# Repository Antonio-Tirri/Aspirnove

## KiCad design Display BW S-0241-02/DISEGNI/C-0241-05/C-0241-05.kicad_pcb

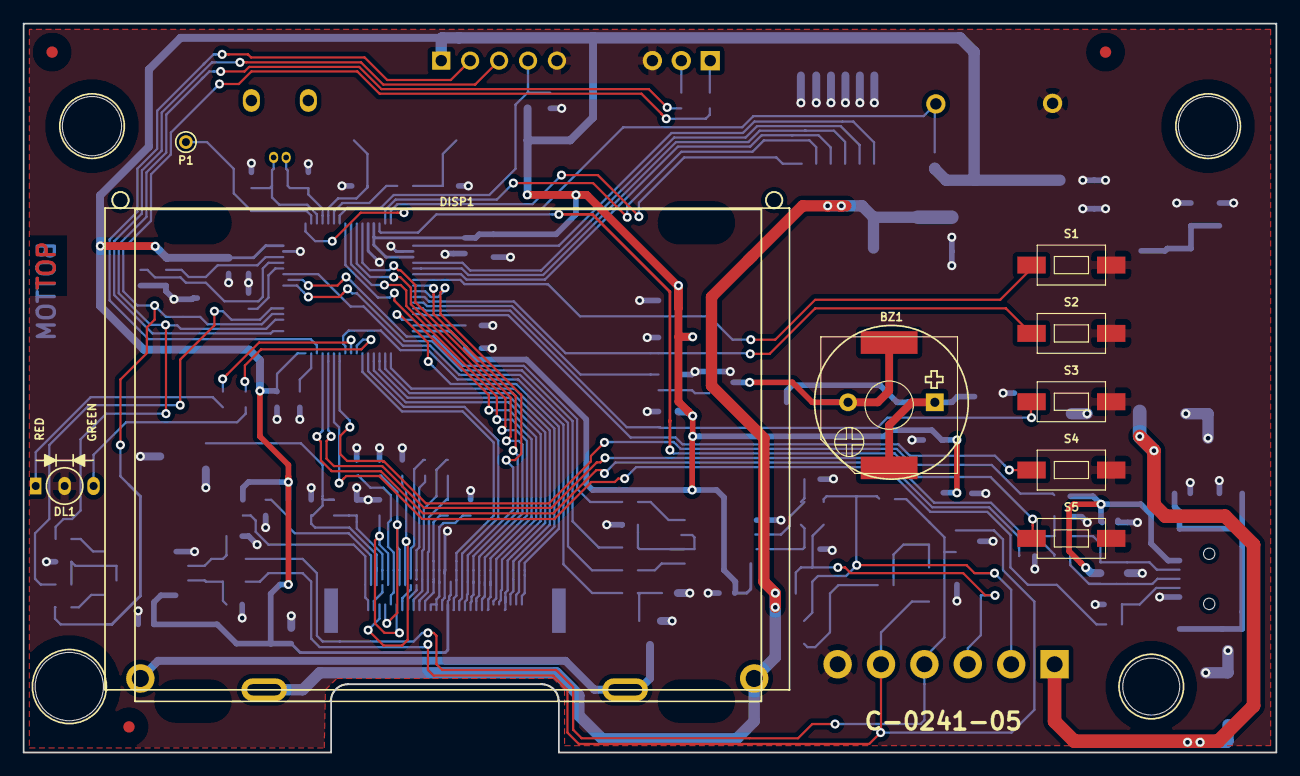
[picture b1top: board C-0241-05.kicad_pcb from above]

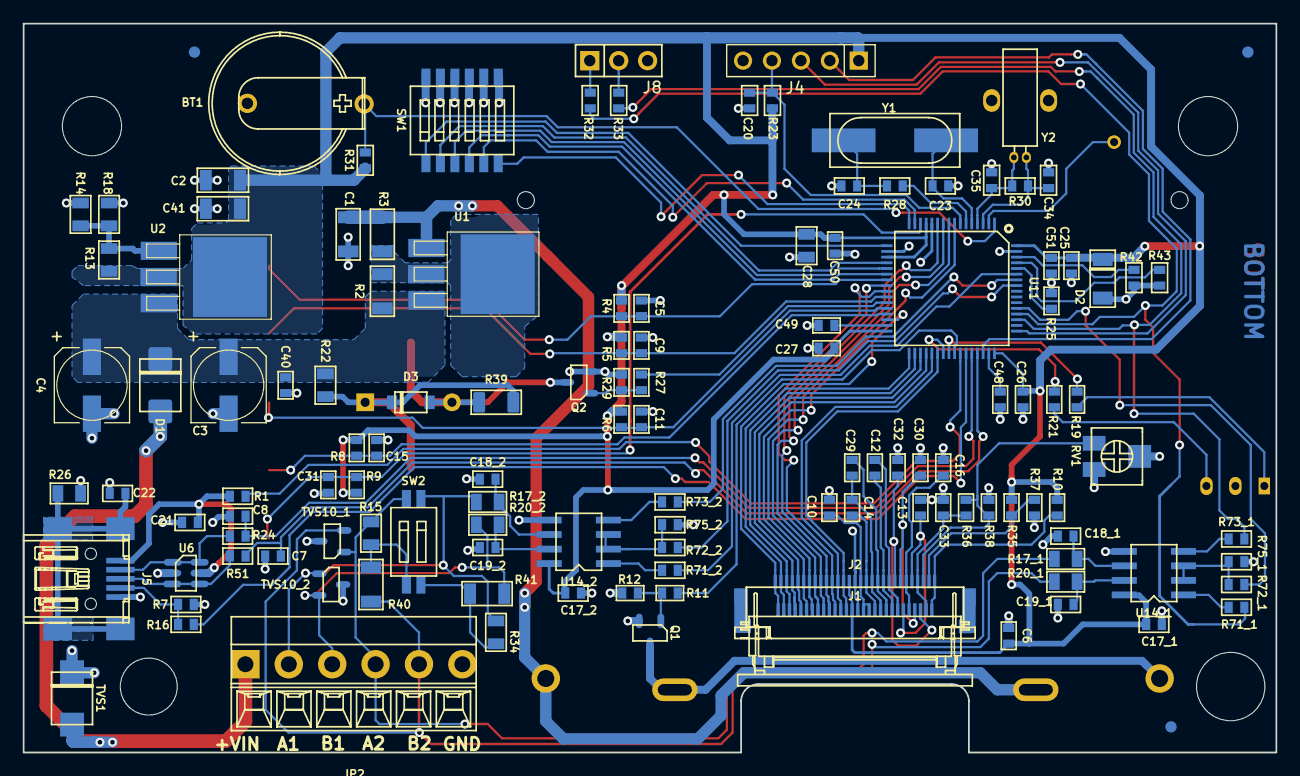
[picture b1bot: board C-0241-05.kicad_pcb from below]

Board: 2 copper layers, 110.0 x 64.0 mm, 135 parts (124 on the bottom side), 101 nets.

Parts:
BT1: CR-1220/HFN; CR1220_HFN
BZ1: LPT1230S-HL-03-4.0-1; KPEG242
BZ1A: LPT1230S-HL-03-4.0-1
C1, C2, C41: 10uF; C1206
C3, C4: 47uF; ELE-D-660
C5, C9, C11, C13, C15, C16, C20, C21, C22, C25, C26, C27, C30, C31, C32, C33, C40, C50, C51: 100nF; C0603
C6, C10, C12, C14, C17_1, C17_2, C29: 1uF; C0603
C7, C8, C23, C24, C34, C35: 12pF; C0603
C18_1, C18_2, C19_1, C19_2: 1nF; C0603
C28: 4.7uF; C0805
C48, C49: 2.2uF; C0603
D1: S2M; D_SMB_DO-214AA_AK
D2: 3.9VZ; D_MiniMELF_SOD80_AK
D3: 1N4148; D_SOD-123_AK
DISP1: G64128W20NBW00; CCT_G64128W20NBW00
DISP2: RX12864A1-BIW; RAYSTAR_RX12864A1-YHY
DL1: BILED; KINGBRIGHT_L-93WSURKCGKC_A1A2K
J1: 52437-2833; Molex_52437-2833
J2: 52435-2933; Molex_52435-2933_Special_Display_RX12864A1-YHY
J4: STRIP2.54-1X5-H11.6-M; SIX5
J5: 65100516121; WURTH_65100516121
J8: STRIP2.54-1X3-H11.6-M; SIX3
JP2: 691508110306; WURTH_691221320006
P1: PAD; PAD_1.2mm_H0.7mm
Q1, Q2: BC817; SOT-23
R1, R7, R16, R25, R31, R42, R43: 0; R0603
R2: 0; R1206
R3: 33; R1206
R4, R5, R6, R8, R9, R10, R12, R23, R29, R35, R37, R75_1, R75_2: 10K; R0603
R11, R27: 22K; R0603
R13: 470; R0805
R14, R18: 1.5K; R0805
R15, R34: 0; R0805
R17_1, R17_2, R20_1, R20_2: 4.7; R0805
R19, R21: 100; R0603
R22: 10; R0805
R24, R51: 10; R0603
R26: 1M; R0805
R28: 220; R0603
R30: 1M; R0603
R32, R33, R71_1, R71_2, R72_1, R72_2, R73_1, R73_2: 1K; R0603
R36: 1.8M; R0603
R38: 330K; R0603
R39: 2.2K; R1206
R40, R41: 120; R1206
RV1: 1M; BOURNS_3314J-1
S1, S2, S3, S4, S5: TVBM11
SW1: GDH06S04; TE_GDH06S04
SW2: GDH02S04; TE_GDH02S04
TVS1: SM6T18CA; D_SMB_DO-214AA
TVS10_1, TVS10_2: CDSOT23-SM712; SOT-23
U1, U2: LM1117IDTX-ADJ/NOPB; TO-252-3Lead_4TAB
U6: USBLC6-2SC6; SOT-23-6_SC74
U11: STM32F205RCT6; QFP-64_10x10mm_Pitch0.5mm
U14_1, U14_2: SN65HVD75D; SOIC-8_3.9x4.9mm_Pitch1.27mm
Y1: 12MHz; Crystal_SMD_HC49
Y2: 32.768kHz; AB38T_Horizontal_Reverse

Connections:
512Hz_OUT: P1.1, U11.2
BL-: DISP1.K, DISP2.K, Q1.3
BUZZER: R27.1, U11.27
C1+: C29.1, J1.20, J2.11
C1-: C14.1, C29.2, J1.19, J2.12
C2+: C12.1, J1.21, J2.10
C2-: C12.2, J1.22, J2.9
C3+: C14.2, J1.18, J2.13
DIP_1: SW1.1, U11.17
DIP_2: SW1.2, U11.20
DIP_3: SW1.3, U11.21
DIP_4: SW1.4, U11.22
DIP_5: SW1.5, U11.15
DIP_6: SW1.6, U11.16
GND: BT1.-, C1.2, C2.2, C3.2, C4.2, C5.1, C6.1, C7.2, C8.2, C9.1, C10.1, C11.1, C13.2, C15.1, C16.2, C17_1.2, C17_2.2, C18_1.2, C18_2.2, C19_1.2, C19_2.2, C20.2, C21.2, C22.2, C23.2, C24.2, C25.2, C26.2, C27.2, C28.2, C30.2, C31.1, C32.2, C33.2, C34.2, C35.2, C40.2, C41.2, C48.2, C49.2, C50.2, C51.2, D2.A, DL1.K, J1.15, J2.15, J4.5, J5.5, J8.3, JP2.6, Q1.2, Q2.2, R7.2, R12.2, R14.2, R18.2, R25.1, R26.2, R29.2, R37.1, R38.1, R42.2, R43.2, R75_1.2, R75_2.2, RV1.1, RV1.2, S1.1, S2.1, S3.1, S4.1, S5.1, SW1.7, SW1.8, SW1.9, SW1.10, SW1.11, SW1.12, TVS1.1, TVS10_1.3, TVS10_2.3, U6.2, U11.12, U11.18, U11.63, U14_1.5, U14_2.5
HW_SEL0: R43.1, U11.61
HW_SEL1: R42.1, U11.62
JTAG_RESET: C20.1, J4.4, R23.2, U11.7
JTAG_SWCLK: J4.3, U11.49
JTAG_SWDIO: J4.2, U11.46
LCD_CLR: J1.2, J2.28, U11.33
LCD_CS: J1.1, J2.29, U11.30
LCD_D0: J1.6, J2.24, U11.8
LCD_D1: J1.7, J2.23, U11.9
LCD_D2: J1.8, J2.22, U11.10
LCD_D3: J1.9, J2.21, U11.11
LCD_D4: J1.10, J2.20, U11.24
LCD_D5: J1.11, J2.19, U11.25
LCD_D6: J1.12, J2.18, U11.37
LCD_D7: J1.13, J2.17, U11.38
LCD_EN: J1.5, J2.25, U11.36
LCD_PWM: R11.1, U11.41
LCD_RS: J1.3, J2.27, U11.34
LCD_RW: J1.4, J2.26, U11.35
LED_R: R19.2, U11.40
LED_V: R21.2, U11.39
NetBT1_+: BT1.+, R31.1, U11.1
NetBZ1_1: BZ1.1, BZ1A.1, D3.K, R22.1, R39.1
NetBZ1_2: BZ1.2, BZ1A.2, D3.A, Q2.3, R39.2
NetC18_1_1: C18_1.1, R17_1.2, U14_1.6
NetC18_2_1: C18_2.1, R17_2.2, U14_2.6
NetC19_1_1: C19_1.1, R20_1.2, U14_1.7
NetC19_2_1: C19_2.1, R20_2.2, U14_2.7
NetC22_1: C22.1, J5.S, R26.1
NetC23_1: C23.1, U11.5, Y1.1
NetC24_1: C24.1, R28.2, Y1.2
NetC34_1: C34.1, R30.2, U11.3, Y2.1
NetC35_1: C35.1, R30.1, U11.4, Y2.2
NetC48_1: C48.1, U11.47
NetC49_1: C49.1, U11.31
NetDL1_A1: DL1.A1, R19.1
NetDL1_A2: DL1.A2, R21.1
NetJ2_2: J2.2, R35.1, R37.2
NetJ2_3: J2.3, R36.1, R38.2, RV1.3
NetJ5_4: J5.4, R7.1, R16.1
NetJ8_1: J8.1, R32.1
NetJ8_2: J8.2, R33.1
NetQ1_1: Q1.1, R11.2, R12.1
NetQ2_1: Q2.1, R27.2, R29.1
NetR1_2: R1.2, U11.42
NetR2_1: R2.1, R3.2, U1.2, U1.4
NetR13_2: R13.2, R14.1, R18.1, U2.1
NetR15_2: R15.2, R40.2, SW2.3
NetR25_2: R25.2, U11.60
NetR28_1: R28.1, U11.6
NetR34_2: R34.2, R41.2, SW2.4
NetR71_1_1: R71_1.1, U14_1.1
NetR71_2_1: R71_2.1, U14_2.1
NetR72_1_2: R72_1.2, R75_1.1, U14_1.2, U14_1.3
NetR72_2_2: R72_2.2, R75_2.1, U14_2.2, U14_2.3
NetR73_1_2: R73_1.2, U14_1.4
NetR73_2_2: R73_2.2, U14_2.4
PS: J1.28, J2.1, R10.1
RS485_A_1: JP2.4, R15.1, R17_1.1, SW2.2, TVS10_1.1
RS485_A_2: JP2.2, R17_2.1, R34.1, SW2.1, TVS10_2.1
RS485_B_1: JP2.5, R20_1.1, R40.1, TVS10_1.2
RS485_B_2: JP2.3, R20_2.1, R41.1, TVS10_2.2
RS485_DIR_1: R72_1.1, R72_2.1, U11.53, U11.57
RS485_RX_1: R32.2, R71_1.2, R71_2.2, U11.52, U11.59
RS485_TX_1: R33.2, R73_1.1, R73_2.1, U11.51, U11.58
SW1: C5.2, R4.2, S1.2, U11.23
SW2: C9.2, R5.2, S2.2, U11.26
SW3: C11.2, R6.2, S3.2, U11.28
SW4: C15.2, R8.2, S4.2, U11.29
SW5: C31.2, R9.2, S5.2, U11.14
USB_DN: C8.1, R24.1, U11.44
USB_DP: C7.1, R51.1, U11.45
USB_ID: R16.2, U11.43
USB_N: J5.2, R24.2, U6.1, U6.6
USB_P: J5.3, R51.2, U6.3, U6.4
V0: C33.1, J1.27, J2.4, R36.2
V1: C13.1, J1.23, J2.5
V2: C16.1, J1.24, J2.6
V3: C30.1, J1.25, J2.7
V4: C32.1, J1.26, J2.8
VCC_3V3: C2.1, C6.2, C17_1.1, C17_2.1, C25.1, C26.1, C27.1, C28.1, C41.1, C50.1, C51.1, D2.K, J1.14, J2.16, J4.1, R4.1, R5.1, R6.1, R8.1, R9.1, R10.2, R13.1, R23.1, R31.2, R35.2, U2.2, U2.4, U11.13, U11.19, U11.32, U11.48, U11.64, U14_1.8, U14_2.8
VCC_12V: C3.1, C4.1, C40.1, D1.K, R2.2, R22.2, U1.3, U2.3
VCC_ALIM: D1.A, JP2.1, TVS1.2
VCC_BACKLIGHT: C1.1, DISP1.A, DISP2.A, R3.1, U1.1
VCC_VUSB: C21.1, J5.1, R1.1, U6.5
VOUT: C10.2, J1.16, J1.17, J2.14

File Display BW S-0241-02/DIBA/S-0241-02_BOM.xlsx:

Progetto: |  |  | Scheda Display
Codice scheda: |  |  | S-0241-02
Variante: |  |  | 002
Revisione: |  |  | 02
Data report: |  |  | 13/11/2020 | Agg.: | 10/11/2021 | 15/12/2021
# | Riferimento | Valore | Descrizione | Costruttore | P/N Costruttore | Contenitore | Quantità | Note
# | Designator | Value | Description | Manufacturer | Manufacturer Part Number | Package | Quantity | AssemblyNotes
1 |  |  |  |  |  |  | 1 | ELC-0241-05
2 | BZ1 | LPT1230S-HL-03-4.0-1 | Piezo Buzzer | Cre-sound | LPT1230S-HL-03-4.0-1 | SMD | 1 | REBZ90003
3 | C1, C2, C41 | 10uF 25V | MLCC Capacitor, 10uF 25V, ±10%, X7R, Case 1206 | Avx | 12063C106KAT2A | 1206 | 3 | RECD93014
4 | C3, C4 | 47uF 25V | SMD Aluminum Electrolytic Capacitor, 47uF 25V, 6.3mm x 5.8mm | Panasonic | EEEFK1E470P | SMD 6.3mm x 5.8mm | 2 | RECD81000
5 | C5, C9, C11, C13, C15, C16, C30, C31, C32, C33 C20, C21, C22, C25, C26, C27, C4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 | 100nF 50V | Multilayer Ceramic Capacitor | Panasonic / TDK / Kemet | ECJ1VB1H104 | 0603 | 19 | RECD95018
6 | C6, C10, C12, C14, C29 C17_1, C17_2 | 1uF 50V | Multilayer Ceramic Chip Capacitor, 1uF 50V, 0603, X7R, 10% | Panasonic / TDK / Kemet | CGA3E2X7R1H102K080AD | 0603 | 7 | RECD95033
7 | C7, C8, C23, C24 | 12pF 50V | MLCC Capacitor, 12pF 50V, ±10%, C0G, Case 0603 | AVX Corp. | 06035A120KAT2A | 0603 | 4 | RECD95026
8 | C18_1, C18_2, C19_1, C19_2 | 1nF 50V | MLCC Capacitor, 1nF 50V, ±10%, C0G, Case 0603 | Avx | 06035C102KAT2A | 0603 | 4 | RECD95011
9 | C28 | 4.7uF 16V | MLCC Capacitor, 4.7uF 16V, ±10%, X7R, Case 0805 | Avx | 0805YC475KAT2A | 0805 | 1 | RECD92028
10 | C48, C49 | 2.2uF 25V | MLCC Capacitor, 2.2uF 25V, ±10%, X5R, Case 0603 | Samsung | CL10A225KA8NNNC | 0603 | 2 | RECD95023
11 | D1 | S2M | Rectifier Diode, 1KV, 1.5A, SMB | DC Components | S2M | SMB | 1 | REDD91002
12 | D3 | 1N4148 | Small Signal Diode, 100V, 150mA, SOD-123 | Diodes Inc. | 1N4148W-7-F | SOD123 | 1 | REDD91035
13 | DISP1 | G64128W20NBW00 | LCD Graphic Display, 128x64, Blue | CCT | G64128W20NBW00 | MECH | 1 | ELC-0241-05
14 | DL1 | BILED 3mm | BICOLOR LED 3mm common cathode | Kingbright | L-93WSURKCGKC | PTH | 1 | A-1132-00
15 | J1 |  | FFC/FPC Connector 29-way | Molex |  | SMD | 1 | RECN90024
16 | J4 | STRIP2.54-1X5-H11.6-M | 5-Way Pin Strip, Single Row, 2.54mm pitch, Male | Adimpex | LE022005-R | PTH | 1 | A-0559-00
17 | J5 | 65100516121 | Mini-USB connector, Type B , Vertical, PTH | Wurth | 65100516121 | SMD | 1 | RECN90017
18 | JP2 | 691221320006 | Morsettiera 6vie , passo 3.5mm, SMD | Wurth | 691221320006 | PTH | 1 | A-1308-00
19 | Q1, Q2 | BC817 | NPN Silicon Transistor, Small signals | NXP Semiconductors | BC817 | SOT-23 | 2 | RETR93010
20 | R1, R7, R16, R25, R31, R42, R43 | 0 | SMD Resistor, 0R, Case 0603 | Vishay | CRCW06030000Z0TABC | 0603 | 7 | RERS95000
21 | R18 | 1.5K 1% | SMD Resistor, 1.5K, Tolerance 1%, Case 0805 |  | CRCW08051K50FKTABC | 0805 | 1 | RERS93108
22 | R3 | 33 1% | SMD Resistor, 33 Ohm, Tolerance 1%, Case 1206 | Vishay | CRCW120633R0FKTA | 1206 | 1 | RERS91095
23 | R4, R5, R6, R8, R9, R75_1, R75_2, R10, R12,R23, R29 | 10K 1% | SMD Resistor, 10K, Tolerance 1%, Case 0603 | Vishay | CRCW060310K0FKTABC | 0603 | 12 | RERS95570
24 | R11, R27 | 22K 1% | SMD Resistor, 22K, Tolerance 1%, Case 0603 | Vishay | CRCW060322K0FKTABC | 0603 | 2 | RERS95576
25 | R13 | 470 1% | SMD Resistor, 470 Ohm, Tolerance 1%, Case 0805 | Vishay | CRCW0805470RFKTABC | 0805 | 1 | RERS93116
26 | R14 | 1.5K 1% | SMD Resistor, 1.5K, Tolerance 1%, Case 0805 | Vishay | CRCW08051K50FKTABC | 0805 | 1 | RERS93108
27 | R17_1, R17_2, R20_1, R20_2 | 4.7 1% | SMD Resistor, 4.7 Ohm, Tolerance 1%, Case 0805 | Vishay | CRCW080544R70FKTABC | 0805 | 4 | RERS93110
28 | R19, R21 | 100 1% | SMD Resistor, 100 Ohm, Tolerance 1%, Case 0603 | Vishay | CRCW0603100RFKTABC | 0603 | 2 | RERS95510
29 | R22 | 10 1% | SMD Resistor, 10 Ohm, Tolerance 1%, Case 0805 | Vishay | CRCW080510R0FKTABC | 0805 | 1 | RERS93000
30 | R24, R51 | 10 1% | SMD Resistor, 10Ohm, Tolerance 1%, Case 0603 | Vishay | CRCW060310R0FKTABC | 0603 | 2 | RERS95500
31 | R26 | 1M 1% | SMD Resistor, 1M, Tolerance 1%, Case 0805 | Vishay | CRCW08051M00FKTA | 0805 | 1 | RERS93050
32 | R36 | 1.8M 1% | RES. SMD 1,8M 0603 1% |  |  | 0603 | 1 | RERS95609
33 | R38 | 330K 1% | RES. SMD 330K 0603 1% |  |  | 0603 | 1 | RERS95610
34 | R28 | 220 1% | SMD Resistor, 220 Ohm, Tolerance 1%, Case 0603 | Vishay | CRCW0603220RFKTABC | 0603 | 1 | RERS95009
35 | R32, R33, R71_1, R71_2 ,R72_1, R72_2, R73_1, R73_2 | 1K 1% | SMD Resistor, 1K, Tolerance 1%, Case 0603 | Vishay | CRCW06031K00FKTABC | 0603 | 8 | RERS95550
36 | R39 | 2.2K 1% | SMD Resistor, 2.2K, Tolerance 1%, Case 1206 | Vishay | CRCW12062K20FKTABC | 1206 | 1 | RERS91112
37 | R40, R41 | 120 1% | SMD Resistor, 120 Ohm, Tolerance 1%, Case 1206 | Vishay | CRCW1206120RFKTABC | 1206 | 2 | RERS91057
38 | S1, S2, S3, S4, S5 | TVBM11 | Tactile switch, 3.5x6 | Bentex | TVBM11 | SMD | 5 | REPL92014
39 | SW2 | GDH02S04 | DIP Switch, 2 Position, SPST, 1.27mm pitch | TE Connectivity | GDH02S04 | SMD | 1 | REDS20002
40 | TVS1 | SM6T18CA | Bidirectional Transil, 600W, 18V, SMB | Stmicroelectronics | SM6T18CA | SMB | 1 | REDD91052
41 | TVS10_1, TVS10_2 | CDSOT23-SM712 | Dual 7V/12V Transient Voltage Suppressor | Bourns | CDSOT23-SM712 | SOT23 | 2 | REDD90022
42 | U1 U2 | LM1117IDTX-ADJ/NOPB | 800mA Low-Dropout Linear Regulator | Texas Instruments | LM1117IDTX-ADJ/NOPB | DPAK | 2 | REIC99171
44 | U6 | USBLC6-2SC6 | ESD Protection Array, USB2.0 | Stmicroelectronics | USBLC6-2SC6 | SOT23-6 | 1 | REDD92023
45 | U11 | STM32F205RCT6 | ARM Cortex M3 , 256K Flash 96K Ram, LQFP 64pin | ST Microelectronics | STM32F205RCT6 | LQFP64 | 1 | REIC99172
46 | U14_1, U14_2 | SN65HVD75D | Low Power RS485 Transceiver, Half Duplex, 3-3,6V, 20Mbps | Texas Instruments | SN65HVD75D | SOIC8 | 2 | REIC93185
47 | Y1 | 12MHz | SMD Quartz Crystal 12MHz, 50ppm | Abracon | ABLS-12.000MHZ-B4-T | HC49 | 1 | REQZ93023
 |  |  |  |  |  |  |  | ELSTAFFA
 |  |  |  |  |  |  |  | ELFRONTALE
 |  |  |  |  |  |  |  | ELVETRINO
 |  |  |  |  |  |  |  | ELFONDO
 |  |  |  |  |  |  |  | ELTASTIERA
 |  |  |  |  |  |  |  | ELDISPLAY64X128_29P
 |  |  |  |  |  |  |  | ELSCATOLA

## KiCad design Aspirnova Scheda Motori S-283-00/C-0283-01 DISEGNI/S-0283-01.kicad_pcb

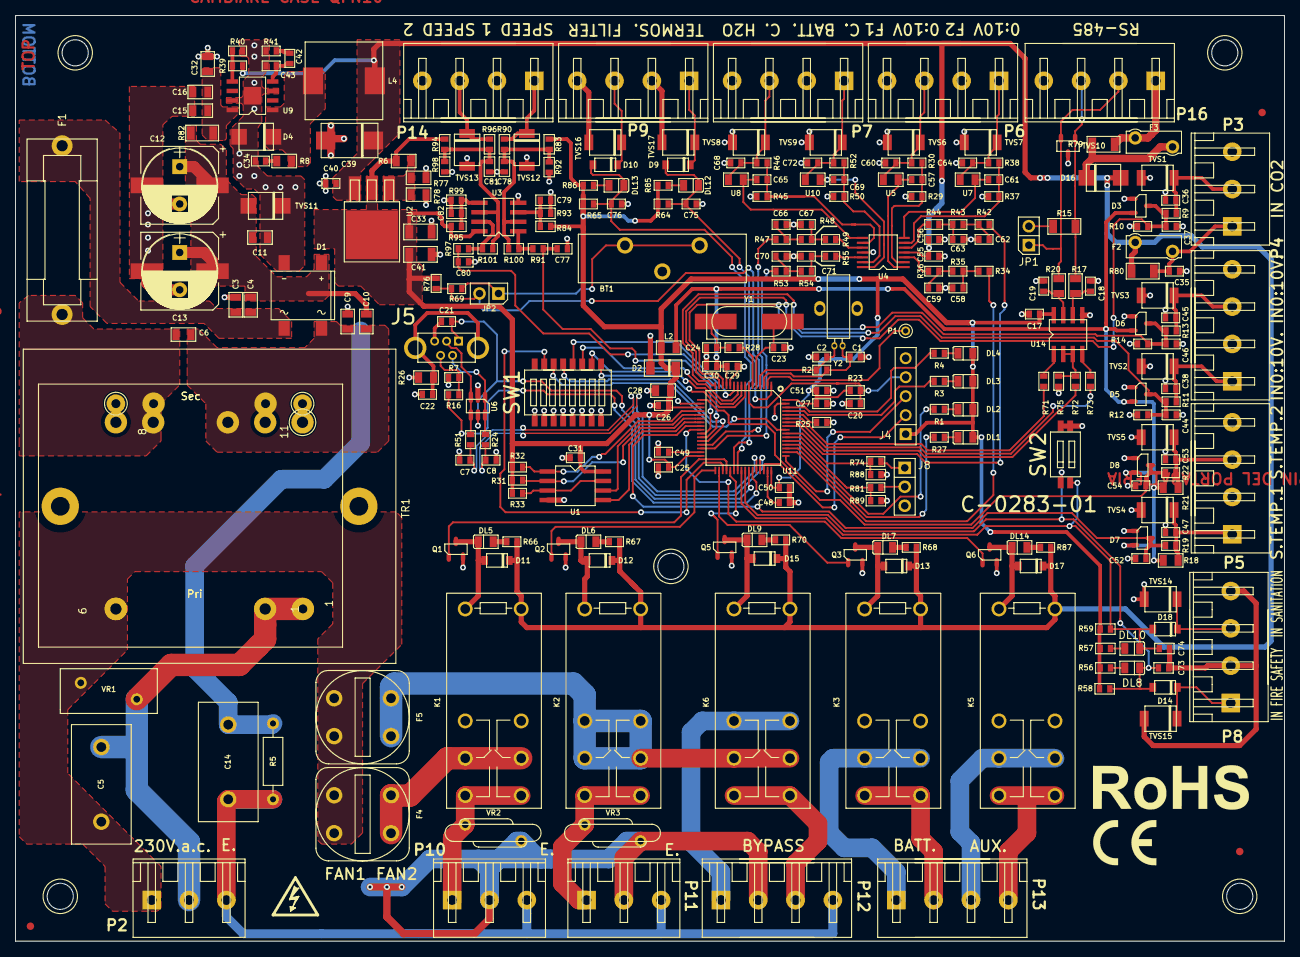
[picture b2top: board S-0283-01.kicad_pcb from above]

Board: 2 copper layers, 170.0 x 124.0 mm, 285 parts (0 on the bottom side), 163 nets.

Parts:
BT1: CR-1220/HFN; ADIMPEX_GR000250-R
C1, C2, C7, C8, C23, C24: 12pF; C0603
C3, C4, C9, C10: 10nF; C0805
C5, C14: 100nF; CAP_L16_W8_P10
C6, C11, C15: 100nF; C0805
C12, C13: 470uF; ELE-G-1030
C16, C32: 1uF; C0805
C17, C37, C44, C46, C52, C54, C55, C58, C59, C62, C63, C66, C67, C70, C71: 1uF; C0603
C18, C19: 1nF; C0603
C20, C21, C22, C25, C26, C27, C31, C35, C40, C50, C51, C56, C73, C74, C75, C76: 100nF; C0603
C28: 4.7uF; C0805
C29, C36, C38, C42, C45, C47, C53, C60, C64, C68, C72, C77, C78, C79, C80, C81, C82: 10nF; C0603
C30: 1uf; C0603
C33, C41: 10uF; C1206
C34: 150pF; C0603
C39: 100uF; Tant_Case-D-7343
C43, C57, C61, C65, C69: 100pF; C0603
C48, C49: 2.2uF; C0603
D1: DF04S; DF04S_1234
D2: 3.9VZ; D_MiniMELF_SOD80_AK
D3, D5, D6, D7, D8: BAV199; SOT-23_A1_K2_N
D4: STPS340U; D_SMB_DO-214AA_AK
D9, D10, D11, D12, D13, D14, D15, D17, D18: 1N4148; D_SOD-123_AK
D16: S2M; D_SMB_DO-214AA_AK
DL1, DL2, DL3, DL4, DL5, DL6, DL7, DL8, DL9, DL10, DL12, DL13, DL14: LED; LED0805_AK
F1: 5x20; STLEVIO_PTF78
F2, F3: 72V,; PTC_7.2x3mm_Pitch5mm
F4, F5: 5x20; SCHURTER_FPG4
J4: STRIP2.54-1X5-H11.6-M; SIX5
J5: 651005136421; WURTH_651005136421
J8: STRIP2.54-1X3-H11.6-M; SIX3
JP1, JP2: JMP2; SIX2
K1, K2, K3, K5, K6: HF115FK/12-Z3T; OMRON_G2R2_PINOUT_ESBI_SPECIAL_2
L2: HZ0805C202R-10; L0805
L4: 15uH; EPCOS_B82464P4153M000
P1: PAD; PAD_1.2mm_H0.7mm
P2, P3, P10, P11: CUM5/3; STELVIO_CUM-5_3
P4, P5, P6, P7, P8, P9, P12, P13, P14, P16: CUM5/4; STELVIO_CUM-5_4
Q1, Q2, Q3, Q5, Q6: PDTC143ET,215; SOT-23
R1, R3, R4, R27: 330; R0603
R2: 1M; R0603
R5: 1K; R_Axial_0.250W_L6.3mm_D2.5mm_P10.16mm_Horizontal
R6: 470; R0805
R7, R16, R25, R69, R76, R88, R89, R100, R101: 0; R0603
R8, R17, R20: 4.7; R0805
R9, R11, R13, R23, R31, R32, R33, R39, R41, R58, R59, R64, R65, R75: 10K; R0603
R10, R12, R14: 3.9K; R0603
R15: 120; R1206
R18, R21: 4.7K; R0805
R19, R22, R71, R72, R73, R74, R81: 1K; R0603
R24, R51: 10; R0603
R26: 1M; R0805
R28: 220; R0603
R29, R37, R45, R50: 12K; R0603
R30, R38, R46, R52: 27K; R0603
R34, R35, R36, R42, R43, R44, R47, R48, R49, R53, R54, R55, R66, R67, R68, R70, R87: 4.7K; R0603
R40: 1.1K; R0603
R56, R57, R85, R86: 560; R0603
R77, R78: 1.5K; R0805
R79, R80, R82: 0; R1206
R83, R84, R93, R94, R95, R99: 47K; R0603
R90, R91, R96, R97: 100; R0603
R92, R98: 5.6K; R0603
SW1: GDH08S04; TE_GDH08S04
SW2: GDH02S04; TE_GDH02S04
TR1: 15V; MYRRA_44194
TVS1, TVS2, TVS3, TVS4, TVS5, TVS6, TVS7, TVS8, TVS9, TVS12, TVS13, TVS14, TVS15, TVS16, TVS17: PTVS13VP1UTP; D_SOD-128_AK
TVS10: CDSOT23-SM712; SOT-23
TVS11: SM6T30CA; D_SMB_DO-214AA
U1: S25FL164K0XMFI011; SOIC-8W_5.3x5.3mm_Pitch1.27mm
U2: LM1117IDTX-ADJ/NOPB; TO-252-3Lead_4TAB
U3: TS922ID; SOIC-8_3.9x4.9mm_Pitch1.27mm
U4: LM224DTBR2G; TSSOP-14_4.4x5mm_Pitch0.65mm
U5, U7, U8, U10: 10; R0805
U6: USBLC6-2SC6; SOT-23-6_SC74
U9: L5973D013TR; SOIC-8-1EP_3.9x4.9mm_Pitch1.27mm
U11: STM32F205RCT6; QFP-64_10x10mm_Pitch0.5mm
U14: SN65HVD75D; SOIC-8_3.9x4.9mm_Pitch1.27mm
VR1, VR2, VR3: S14K275E; RV_Disc_D13_W6_P7.5
Y1: 12MHz; Crystal_SMD_HC49
Y2: 32.768kHz; AB38T_Horizontal_Reverse

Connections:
512Hz_OUT: P1.1, U11.2
AGND: BT1.-, C1.2, C2.2, C3.2, C7.2, C8.2, C9.1, C11.2, C12.2, C13.2, C14.2, C15.2, C16.2, C17.2, C18.2, C19.2, C20.2, C21.2, C22.2, C23.2, C24.2, C25.2, C26.2, C27.2, C28.2, C29.2, C30.2, C31.2, C32.2, C33.2, C34.2, C35.2, C36.2, C37.2, C38.2, C39.2, C40.2, C41.2, C43.2, C44.2, C45.2, C46.2, C47.2, C48.2, C49.2, C50.2, C51.2, C52.2, C53.2, C54.2, C55.2, C56.2, C58.2, C59.2, C60.2, C62.2, C63.2, C64.2, C66.2, C67.2, C68.2, C70.2, C71.2, C72.2, C73.2, C74.2, C75.2, C76.2, C77.2, C78.2, C79.1, C80.2, C81.2, C82.1, D1.2, D2.A, D3.A1, D4.A, D5.A1, D6.A1, D7.A1, D8.A1, J4.5, J5.5, J8.3, P3.3, P4.2, P4.4, P5.2, P5.4, P6.2, P6.4, P7.2, P7.4, P8.2, P8.4, P9.2, P9.4, P14.2, P14.4, P16.4, Q1.2, Q2.2, Q3.2, Q5.2, Q6.2, R5.2, R7.2, R10.2, R12.2, R14.2, R25.1, R26.2, R29.2, R37.2, R40.2, R41.2, R45.2, R50.2, R75.2, R77.2, R78.2, R88.1, R89.1, R92.2, R93.2, R98.2, R99.2, SW1.10, SW1.11, SW1.12, SW1.13, SW1.14, SW1.15, SW1.16, SW2.3, SW2.4, TVS1.A, TVS2.A, TVS3.A, TVS4.A, TVS5.A, TVS6.A, TVS7.A, TVS8.A, TVS9.A, TVS10.3, TVS11.1, TVS12.A, TVS13.A, TVS14.A, TVS15.A, TVS16.A, TVS17.A, U1.4, U3.4, U4.11, U6.2, U9.3, U9.7, U9.9, U11.12, U11.18, U11.63, U14.5
AN0_CO2: C37.1, D3.N, R9.1, R10.1, U11.14
AN1_AUX1: C44.1, D5.N, R11.1, R12.1, U11.15
AN2_AUX2: C46.1, D6.N, R13.1, R14.1, U11.16
AN2_TEMP_INT: C52.1, D7.N, R19.1, U11.24
AN14_TEMP_EXT: C54.1, D8.N, R22.1, U11.17
ANOUT_BATT: R53.2, U11.30
ANOUT_FAN1: R34.2, U11.50
ANOUT_FAN2: R42.2, U11.55
ANOUT_H2O: R47.2, U11.29
AUX_C: K5.3, K5.6, P13.3
AUX_NO: K5.4, K5.5, P13.4
BATT_C: K3.3, K3.6, P13.1
BATT_NO: K3.4, K3.5, P13.2
BYP_C: C5.1, F4.2, F5.2, P2.1, TR1.5, VR1.2
BYP_NC: K6.2, K6.7, P12.1
BYP_NO: K6.4, K6.5, P12.3
DIN_FILTRO: C76.1, D10.A, DL13.K, R65.2, U11.39
DIN_LV1: C73.1, D14.A, DL8.K, R58.2, SW2.1, U11.41
DIN_LV2: C74.1, D18.A, DL10.K, R59.2, SW2.2, U11.40
DIN_TERMOST: C75.1, D9.A, DL12.K, R64.2, U11.38
DIP_1: SW1.1, U11.8
DIP_2: SW1.2, U11.9
DIP_3: SW1.3, U11.10
DIP_4: SW1.4, U11.11
DIP_5: SW1.5, U11.28
DIP_6: SW1.6, U11.56
DIP_7: SW1.7, U11.35
EARTH: C14.1, P2.3, P10.3, P11.3, P12.4, R5.1
FAN1_C: F4.1, K1.3, K1.6
FAN1_NO: K1.4, K1.5, P10.1, VR2.2
FAN2_C: F5.1, K2.2, K2.3, K2.6, K2.7, K6.3, K6.6
FAN2_NO: K2.4, K2.5, P11.1, VR3.2
FLASH_CS: R32.2, U1.1, U11.20
FLASH_MISO: R31.2, U1.2, U11.22
FLASH_MOSI: U1.5, U11.23
FLASH_SCK: U1.6, U11.21
IN_AUX1: C38.1, P4.1, R11.2, TVS2.K
IN_AUX2: C45.1, P4.3, R13.2, TVS3.K
IN_CO2: C36.1, P3.2, R9.2, TVS1.K
JTAG_RESET: C20.1, J4.4, R23.2, U11.7
JTAG_SWCLK: J4.3, U11.49
JTAG_SWDIO: J4.2, U11.46
LED_ERR: R27.2, U11.51
LED_ON: R1.2, U11.52
LED_PC1: R3.2, U11.61
LED_PC2: R4.2, U11.62
MAIN_N: C5.2, P2.2, P10.2, P11.2, P12.2, TR1.1, VR1.1, VR2.1, VR3.1
NetBT1_+: BT1.+, JP2.1, R69.1
NetC1_1: C1.1, R2.2, U11.3, Y2.1
NetC2_1: C2.1, R2.1, U11.4, Y2.2
NetC3_1: C3.1, C4.1, D1.3, F1.2
NetC4_2: C4.2, C10.1, C11.1, C12.1, C13.1, D1.1, R82.2, TVS11.2
NetC6_1: C6.1, F1.1, TR1.7
NetC6_2: C6.2, C9.2, C10.2, D1.4, TR1.9
NetC18_1: C18.1, R17.2, U14.6
NetC19_1: C19.1, R20.2, U14.7
NetC22_1: C22.1, J5.S, R26.1
NetC23_1: C23.1, U11.5, Y1.1
NetC24_1: C24.1, R28.2, Y1.2
NetC34_1: C34.1, R8.2
NetC35_1: C35.1, F2.1, P3.1, R80.2
NetC42_1: C42.1, C43.1, U9.4
NetC42_2: C42.2, R41.1
NetC47_1: C47.1, P5.1, R18.2, R19.2, TVS4.K
NetC48_1: C48.1, U11.47
NetC49_1: C49.1, U11.31
NetC53_1: C53.1, P5.3, R21.2, R22.2, TVS5.K
NetC57_1: C57.1, R29.1, R30.2, U4.2
NetC57_2: C57.2, U4.1, U5.2
NetC58_1: C58.1, R34.1, R35.2
NetC59_1: C59.1, R35.1, R36.2
NetC60_1: C60.1, P6.3, R30.1, TVS6.K, U5.1
NetC61_1: C61.1, R37.1, R38.2, U4.6
NetC61_2: C61.2, U4.7, U7.2
NetC62_1: C62.1, R42.1, R43.2
NetC63_1: C63.1, R43.1, R44.2
NetC64_1: C64.1, P6.1, R38.1, TVS7.K, U7.1
NetC65_1: C65.1, R45.1, R46.2, U4.9
NetC65_2: C65.2, U4.8, U8.2
NetC66_1: C66.1, R47.1, R48.2
NetC67_1: C67.1, R48.1, R49.2
NetC68_1: C68.1, P7.3, R46.1, TVS8.K, U8.1
NetC69_1: C69.1, R50.1, R52.2, U4.13
NetC69_2: C69.2, U4.14, U10.2
NetC70_1: C70.1, R53.1, R54.2
NetC71_1: C71.1, R54.1, R55.2
NetC72_1: C72.1, P7.1, R52.1, TVS9.K, U10.1
NetC78_1: C78.1, R83.2, R90.2, R92.1, R100.1, U3.2
NetC79_2: C79.2, R84.2, R93.1, U3.3
NetC81_1: C81.1, R94.2, R96.2, R98.1, R101.1, U3.6
NetC82_2: C82.2, R95.2, R99.1, U3.5
NetD4_K: D4.K, L4.1, R8.1, U9.1
NetD9_K: D9.K, P9.1, TVS17.K
NetD10_K: D10.K, P9.3, TVS16.K
NetD11_A: D11.A, DL5.K, K1.1, Q1.3
NetD12_A: D12.A, DL6.K, K2.1, Q2.3
NetD13_A: D13.A, DL7.K, K3.1, Q3.3
NetD14_K: D14.K, P8.1, TVS15.K
NetD15_A: D15.A, DL9.K, K6.1, Q5.3
NetD16_K: D16.K, F3.1, R79.2
NetD17_A: D17.A, DL14.K, K5.1, Q6.3
NetD18_K: D18.K, P8.3, TVS14.K
NetDL1_K: DL1.K, R27.1
NetDL2_K: DL2.K, R1.1
NetDL3_K: DL3.K, R3.1
NetDL4_K: DL4.K, R4.1
NetDL5_A: DL5.A, R66.2
NetDL6_A: DL6.A, R67.2
NetDL7_A: DL7.A, R68.2
NetDL8_A: DL8.A, R56.2
NetDL9_A: DL9.A, R70.2
NetDL10_A: DL10.A, R57.2
NetDL12_A: DL12.A, R85.2
NetDL13_A: DL13.A, R86.2
NetDL14_A: DL14.A, R87.2
NetF3_2: F3.2, P16.1, R79.1
NetJ5_4: J5.4, R7.1, R16.1
NetJ8_1: J8.1, R74.1
NetJ8_2: J8.2, R81.1
NetJP1_2: JP1.2, R15.1
NetJP2_2: JP2.2, R69.2, R76.1, U11.1
NetP14_1: P14.1, R90.1, TVS12.K
NetP14_3: P14.3, R96.1, TVS13.K
NetR6_2: R6.2, R77.1, R78.1, U2.1
NetR25_2: R25.2, U11.60
NetR28_1: R28.1, U11.6
NetR33_2: R33.2, U1.3, U1.7
NetR36_1: R36.1, U4.3
NetR39_2: R39.2, R40.1, U9.5
NetR44_1: R44.1, U4.5
NetR49_1: R49.1, U4.10
NetR55_1: R55.1, U4.12
NetR71_1: R71.1, U14.1
NetR72_2: R72.2, R75.1, U14.2, U14.3
NetR73_2: R73.2, U14.4
NetR91_1: R91.1, R100.2, U3.1
NetR97_1: R97.1, R101.2, U3.7
RELE_AUX1: Q6.1, U11.25
RELE_BATT: Q3.1, U11.34
RELE_BYP: Q5.1, U11.37
RELE_FAN1: Q1.1, U11.36
RELE_FAN2: Q2.1, U11.33
RS485_A: P16.3, R15.2, R17.1, TVS10.1
RS485_B: JP1.1, P16.2, R20.1, TVS10.2
RS485_DIR: R72.1, U11.57
RS485_RX: R71.2, U11.59
RS485_TX: R73.1, U11.58
TACH_F1: C77.1, R91.2, U11.26
TACH_F2: C80.1, R97.2, U11.27
UART5_RX: R74.2, R88.2, U11.54
UART5_TX: R81.2, R89.2, U11.53
USB_DN: C8.1, R24.1, U11.44
USB_DP: C7.1, R51.1, U11.45
USB_ID: R16.2, U11.43
USB_N: J5.2, R24.2, U6.1, U6.6
USB_P: J5.3, R51.2, U6.3, U6.4
VCC_3V3: C17.1, C25.1, C26.1, C27.1, C28.1, C31.1, C33.1, C41.1, C50.1, C51.1, D2.K, DL1.A, DL2.A, DL3.A, DL4.A, J4.1, L2.1, R6.1, R23.1, R31.1, R32.1, R33.1, R56.1, R57.1, R58.1, R59.1, R64.1, R65.1, R76.2, R83.1, R84.1, R85.1, R86.1, R94.1, R95.1, U1.8, U2.2, U2.4, U3.8, U11.19, U11.32, U11.48, U11.64, U14.8
VCC_3V3A: C29.1, C30.1, D3.K2, D5.K2, D6.K2, D7.K2, D8.K2, L2.2, R18.1, R21.1, U11.13
VCC_12V: C39.1, C40.1, C55.1, C56.1, D11.K, D12.K, D13.K, D15.K, D16.A, D17.K, F2.2, K1.8, K2.8, K3.8, K5.8, K6.8, L4.2, R39.1, R66.1, R67.1, R68.1, R70.1, R80.1, R87.1, U2.3, U4.4
VCC_UNREG: C15.1, C16.1, C32.1, R82.1, U9.8
VCC_VUSB: C21.1, J5.1, U6.5, U11.42

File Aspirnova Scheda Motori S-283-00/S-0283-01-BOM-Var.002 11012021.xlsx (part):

Progetto: |  |  | Scheda controllo
Codice scheda: |  |  | S-0283-01
Variante: |  |  | 002
Revisione: |  |  | 01
Data report: |  |  | 29/10/2020 | 11/01/2021
# | Riferimento | Valore | Descrizione | Costruttore | P/N Costruttore | Contenitore | Quantità | Note
# | Designator | Value | Description | Manufacturer | Manufacturer Part Number | Package | Quantity | AssemblyNotes
1 | BT1 | CR-1220/HFN | Battery Lithium 3V coin 12.5 mm | Panasonic | CR-1220/HFN | PTH | 1 | A-1081-00
 | BT1 |  | PORTABATTERIA VERTICALE 2032 GR000250 |  |  |  |  | A-1341-00
 | BT1 |  | BATTERIA 3V 2032 |  |  |  |  | A-1218-00
4 | C1, C2, C7, C8, C23, C24 | 12pF 50V | MLCC Capacitor, 12pF 50V, ±10%, C0G, Case 0603 | AVX Corp. | 06035A120KAT2A | 0603 | 6 | RECD95026
5 | C3, C4, C9, C10 | 10nF 50V | MLCC Capacitor, 10nF 50V, ±10%, X7R, Case 0805 | AVX Corp. | 08055C103KAT2A | 0805 | 4 | RECD92009
6 | C5, C14 | 100nF 275Vac | Condensatore a Film Plastico, 100nF, X2 | Kemet | R46KF310050P0K | PTH | 2 | A-1135-00
7 | C6, C11, C15 | 100nF 50V | MLCC Capacitor, 100nF 50V, ±10%, X7R, Case 0805 | AVX Corp. | 08055C104KAT2A | 0805 | 3 | RECD92013
8 | C12, C13 | 470uF 35V | SMD Aluminum Electrolytic Capacitor, 470uF 35V, 8mm x 10.2mm | Panasonic Electronic Components | EEEFK1V471SP | SMD 10mm x 10.2mm | 2 | a-0779-00
9 | C16, C32 | 1uF 50V | MLCC Capacitor, 1uF 50V, ±10%, X7R, Case 0805 | Murata | GRM21BR71H105K | 0805 | 2 | RECD92021
10 | C17, C30 | 1uF 50V | MLCC Capacitor, 1uF 50V, ±10%, X5R, Case 0603 | Samsung | CL10A105KB8NNNC | 0603 | 2 | RECD95033
11 | C18, C19 | 1nF 50V | MLCC Capacitor, 1nF 50V, ±10%, C0G, Case 0603 | Avx | 06035C102KAT2A | 0603 | 2 | RECD95011
12 | C20, C21, C22, C25, C26, C27, C35, C40, C50, C51 | 100nF 50V | MLCC Capacitor, 100nF 50V, ±10%, X7R, Case 0603 | Avx | 06035C104KAT2A | 0603 | 10 | RECD95018
13 | C28 | 4.7uF 16V | MLCC Capacitor, 4.7uF 16V, ±10%, X7R, Case 0805 | Avx | 0805YC475KAT2A | 0805 | 1 | RECD92023
14 | C29, C42 | 10nF 50V | MLCC Capacitor, 10nF 50V, ±10%, X7R, Case 0603 | Avx | 06035C103KAT2A | 0603 | 2 | RECD95012
15 | C33, C41 | 10uF 25V | MLCC Capacitor, 10uF 25V, ±10%, X7R, Case 1206 | Avx | 12063C106KAT2A | 1206 | 2 | RECD93014
16 | C34 | 150pF 50V | MLCC Capacitor, 150pF 50V, ±10%, C0G, Case 0603 | Avx | 06035A151JAT2A | 0603 | 1 | RECD95009
17 | C36, C38, C45, C47, C53, C60, C64, C68, C72, C77, C78, C79, C80, C81, C82 | 10nF 50V | MLCC Capacitor, 10nF 50V, ±10%, X7R, Case 0603 | Avx | 06035C103KAT2A | 0603 | 15 | RECD95012
18 | C37, C44, C46, C52, C54, C55, C58, C59, C62, C63, C66, C67, C70, C71 | 1uF 50V | MLCC Capacitor, 1uF 50V, ±10%, X5R, Case 0603 | Samsung | CL10A105KB8NNNC | 0603 | 14 | RECD95033
19 | C39 | 100uF TANT 20V | Solid Tantalum Chip Capacitor, 100uF, 20V, TC7343 | Avx | TAJD107K020RNJ | TC7343 | 1 | RECD82016
20 | C43 | 100pF 50V | MLCC Capacitor, 100pF 50V, ±10%, C0G, Case 0603 | Samsung | CL10C101JB8NNNC | 0603 | 1 | RECD95008
21 | C48, C49 | 2.2uF 25V | MLCC Capacitor, 2.2uF 25V, ±10%, X5R, Case 0603 | Samsung | CL10A225KA8NNNC | 0603 | 2 | RECD95023
22 | C56, C73, C74, C75, C76 | 100nF 50V | MLCC Capacitor, 100nF 50V, ±10%, X7R, Case 0603 | Avx | 06035C104KAT2A | 0603 | 5 | RECD95018
23 | C57, C61, C65, C69 | 100pF 50V | MLCC Capacitor, 100pF 50V, ±10%, C0G, Case 0603 | Samsung | CL10C101JB8NNNC | 0603 | 4 | RECD95008
24 | D1 | DF04S | Rectifier Bridge, 400V, 1A, SMD, 1V, SOIC | Vishay | DF04S | SMD | 1 | REDD90010
25 | D3, D5, D6, D7, D8 | BAV199 | Two Small Signal Diodes, 75V, SOT-23 | Infineon | BAV199E6327 | SOT-23 | 5 | REDD92019
26 | D4 | STPS340U | Power Schottky Rectifier, 40V, 3A | Stmicroelectronics | STPS340U | SMB | 1 | REDD96005
27 | D9, D10, D11, D12, D13, D14, D15, D17, D18 | 1N4148 | Small Signal Diode, 100V, 150mA, SOD-123 | Diodes Inc. | 1N4148W-7-F | SOD123 | 9 | REDD91035
28 | D16 | S2M | Rectifier Diode, 1KV, 1.5A, SMB | DC Components | S2M | SMB | 1 | REDD91002
29 | DL1, DL5, DL6, DL7, DL8, DL9, DL10, DL12, DL13, DL14 | LED ROSSO | Red SMD LED | Kingbright | KP-2012SRC-J4 | 0805 | 10 | REDD94009
30 | DL2, DL3, DL4 | LED VERDE | Green SMD LED | Kingbright | KP-2012SGC | 0805 | 3 | REDD94007
31 | F1 | 5x20 | 5x20 Fuse Holder | ECC | PTF/78 | PTH | 1 | A-0396-00
 |  |  |  |  |  |  | 1 | A-0396-00cc
 |  |  | 400ma 5x20 |  |  |  | 1 | A-0146-00
34 | F2, F3 | 72V, 0.20A | PTC Resettable Fuse, 72V, 0.20A | Little Fuse Inc. | 72R020X | Radial, 7.4mm | 2 | A-1138-00
35 | F4,F5 | 5x20 | 5x20 Fuse Holder vertical | SHURTER | FPG4 | PTH | 2 | A-1136-00
 |  |  | 10 5Ax20 |  |  |  | 1 | A1137-00
37 | J4 | STRIP2.54-1X5-H11.6-M | 5-Way Pin Strip, Single Row, 2.54mm pitch, Male | Adimpex | LE022005-R | PTH | 1 | A-1133-00
 | J8 |  | PONTE FILO RIGIDO PIN 2 – 3 |  |  |  | 1 | A-0152-00
39 | J5 | 651005136421 | Mini-USB connector, Type B , Vertical, PTH | Wurth | 651005136421 | PTH | 1 | A-1139-00
40 | JP1 | JMP2 | 2-way Jumper | Adimpex | LE008002-R | PTH | 1 | A-1140-00
41 | K1, K2, K3, K5, K6 | HF115FK/12-Z3T | Single-Pole Dual-Throw Relay, 12VDC, 16A, 250V | Hong Fa | HF115FK/12-Z3T | PTH | 5 | A-0248-00
42 | L2 | HZ0805C202R-10 | Ferrite chip beads Z=2k | Laird Technologies | HZ0805C202R-10 | 0805 | 1 | REIN93028
43 | L4 | 15uH | Power Inductor for Switching Regulator, 2.5A | Epcos | B82464A4153K | SMD 10x10mm | 1 | REIN95002
44 | P2, P3, P10, P11 | CUM5/3 | Stelvio Male PCB Header, 3ways, 5mm pitch | Stelvio | CUM5/3 | PTH | 4 | A-0667-00
 |  |  |  |  |  |  | 4 | A-0666-00
46 | P4, P5, P6, P7, P8, P9, P12, P13, P14, P16 | CUM5/4 | Stelvio Male PCB Header, 4ways, 5mm pitch | Stelvio | CUM5/4 |  | 10 | A-0049-00
 |  |  |  |  |  |  | 10 | A-0048-00
48 | Q1, Q2, Q3, Q5, Q6 | PDTC143ET,215 | NPN Biased transistor, R=4.7K | Nxp | PDTC143ET,215 | SOT-23 | 5 | RETR92026
49 | R1, R3, R4, R27 | 330 1% | SMD Resistor, 330 Ohm, Tolerance 1%, Case 0603 | Yageo | RC0603FR-07330RL | 0603 | 4 | RERS95511
50 | R5 | 1K 0.5W | Resistenza 1K Ohm, 5%, 0.5W, Assiale |  |  | PTH | 1 | A-1141-00
51 | R6 | 470 1% | SMD Resistor, 470 Ohm, Tolerance 1%, Case 0805 | Vishay | CRCW0805470RFKTABC | 0805 | 1 | RERS93116
52 | R7, R16, R25, R69, R88, R89, R81 | 0 | SMD Resistor, 0R, Case 0603 | Vishay | CRCW06030000Z0TABC | 0603 | 6 | RERS95000
53 | R8 | 4.7 1% | SMD Resistor, 4.7 Ohm, Tolerance 1%, Case 0805 | Vishay | CRCW08054R70FKTABC | 0805 | 1 | RERS93110
54 | R9, R11, R13, R58, R59, R64, R65, R75 | 10K 1% | SMD Resistor, 10K, Tolerance 1%, Case 0603 | Vishay | CRCW060310K0FKTABC | 0603 | 8 | RERS95570
55 | R10, R12, R14 | 3.9K 1% | SMD Resistor, 3.9K, Tolerance 1%, Case 0603 | Vishay | CRCW06033K90FKTABC | 0603 | 3 | RERS95532
56 | R15 | 120 1% | SMD Resistor, 120 Ohm, Tolerance 1%, Case 1206 | Vishay | CRCW1206120RFKTABC | 1206 | 1 | RERS91057
57 | R17, R20 | 4.7 1% | SMD Resistor, 4.7 Ohm, Tolerance 1%, Case 0805 | Vishay | CRCW080544R70FKTABC | 0805 | 2 | RERS93110
58 | R18, R21 | 4.7K 1% | SMD Resistor, 4.7K, Tolerance 1%, Case 0805 | Vishay | CRCW08054K70FKTABC | 0805 | 2 | RERS93033
59 | R19, R22, R71 | 1K 1% | SMD Resistor, 1K, Tolerance 1%, Case 0603 | Vishay | CRCW06031K00FKTABC | 0603 | 3 | RERS95550
60 | R23, R39, R41 | 10K 1% | SMD Resistor, 10K, Tolerance 1%, Case 0603 | Vishay | CRCW060310K0FKTABC | 0603 | 3 | RERS95570
61 | R24, R51 | 10 1% | SMD Resistor, 10Ohm, Tolerance 1%, Case 0603 | Vishay | CRCW060310R0FKTABC | 0603 | 2 | RERS95500
62 | R26 | 1M 1% | SMD Resistor, 1M, Tolerance 1%, Case 0805 | Vishay | CRCW08051M00FKTA | 0805 | 1 | RERS93050
63 | R28 | 220 1% | SMD Resistor, 220 Ohm, Tolerance 1%, Case 0603 | Vishay | CRCW0603220RFKTABC | 0603 | 1 | RERS95009
64 | R29, R37, R45, R50 | 12K 1% | SMD Resistor, 12K, Tolerance 1%, Case 0603 | Vishay | CRCW060312K0FKTABC | 0603 | 4 | RERS95572
65 | R30, R38, R46, R52 | 27K 1% | SMD Resistor, 27K, Tolerance 1%, Case 0603 | Vishay | CRCW060327K0FKTABC | 0603 | 4 | RERS95580
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
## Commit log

2024-01-16 start
